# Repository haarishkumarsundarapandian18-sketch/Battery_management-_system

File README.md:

# Battery_management-_system

# CubeSat Battery Management System (BMS)

This project presents the complete development of a **Battery Management System (BMS) for a CubeSat**, starting from battery pack selection and modeling, followed by SoC estimation and BMS circuit development, and finally PCB design, manufacturing, assembly, and testing.

The project can be followed as a step-by-step workflow for developing a BMS from the initial battery requirements to a working hardware prototype.

## Project Workflow

### 1. Define Battery Requirements

Start by identifying the CubeSat's power requirements, including:

* Required battery voltage
* Required capacity
* Maximum and minimum load current
* Charging requirements
* Operating temperature range
* Expected discharge duration

These values are used to determine the required battery configuration and BMS specifications.

### 2. Design the Battery Pack

Select the appropriate battery cell based on the required voltage, capacity, discharge current, size, weight, and application requirements.

Determine the required **series (S) and parallel (P) configuration** and calculate:

* Pack voltage
* Pack capacity
* Maximum current
* Energy capacity

### 3. Build the Battery Model in MATLAB/Simulink

Create a battery model in **MATLAB/Simulink** using the selected cell characteristics.

Simulate the battery under different load conditions and observe:

* Battery voltage
* Current
* State of Charge (SoC)
* Discharge characteristics
* Battery response to changing loads

This step helps validate the battery configuration before moving to hardware development.

### 4. Implement SoC Estimation

Develop the **State of Charge estimation** model in MATLAB.

Use the battery voltage/current data and an appropriate estimation method to determine the remaining battery capacity during operation.

Test the SoC estimation model under different charge and discharge conditions and compare the estimated SoC with the expected battery behavior.

### 5. Develop the BMS Architecture

Define the BMS functions required for the battery pack.

The BMS architecture includes:

* Cell voltage monitoring
* Current sensing
* Temperature monitoring
* SoC estimation
* Battery protection
* Fault detection
* Control and communication

Define the required operating limits for each parameter.

### 6. Design the BMS Circuit

Select the required sensing, protection, control, and power-management components.

Develop the BMS schematic based on the defined architecture and connect:

* Voltage sensing circuits
* Current sensing circuit
* Temperature sensing
* Protection circuitry
* Power supply/regulation
* Controller/interface circuitry

Verify the circuit calculations and component ratings before PCB implementation.

### 7. Design the PCB in KiCad

Create the complete PCB using **KiCad**.

The process includes:

1. Creating the schematic
2. Assigning footprints
3. Creating the PCB layout
4. Placing components
5. Routing power and signal traces
6. Applying appropriate design rules
7. Checking clearances and track widths
8. Running Design Rule Checks (DRC)
9. Preparing the final PCB for manufacturing

Special attention is given to high-current paths, grounding, component placement, thermal considerations, and signal integrity.

### 8. PCB Manufacturing

Generate the required manufacturing files from KiCad and send the design for PCB fabrication.

After receiving the fabricated PCB:

* Inspect the board
* Verify footprints and connections
* Procure the required components
* Solder the components
* Inspect solder joints
* Check for shorts and incorrect connections

### 9. Hardware Testing

Power up the assembled BMS gradually and verify the individual sections before connecting the complete battery pack.

Test:

* Voltage sensing
* Current measurement
* Temperature measurement
* SoC estimation
* Protection functions
* Controller operation
* Communication/interface functions

Compare the measured hardware results with the MATLAB simulations and calculated values.

## Tools Used

* **MATLAB / Simulink** – Battery modeling and SoC estimation
* **KiCad** – Schematic capture and PCB design
* **PCB Fabrication & Assembly** – Hardware implementation
* **Battery Modeling** – Cell and pack characterization
* **BMS Design** – Monitoring and protection
* **Hardware Testing** – Validation of the developed system

## Overall Development Flow

**Battery Requirements → Battery Selection → Battery Pack Design → MATLAB Battery Modeling → SoC Estimation → BMS Architecture → Circuit Design → KiCad Schematic → PCB Layout → Manufacturing → Assembly → Testing & Validation**
# CubeSat Battery Management System (BMS)

This project presents the complete development of a **Battery Management System (BMS) for a CubeSat**, starting from battery pack selection and modeling, followed by SoC estimation and BMS circuit development, and finally PCB design, manufacturing, assembly, and testing.

The project can be followed as a step-by-step workflow for developing a BMS from the initial battery requirements to a working hardware prototype.

## Project Workflow

### 1. Define Battery Requirements

Start by identifying the CubeSat's power requirements, including:

* Required battery voltage
* Required capacity
* Maximum and minimum load current
* Charging requirements
* Operating temperature range
* Expected discharge duration

These values are used to determine the required battery configuration and BMS specifications.

### 2. Design the Battery Pack

Select the appropriate battery cell based on the required voltage, capacity, discharge current, size, weight, and application requirements.

Determine the required **series (S) and parallel (P) configuration** and calculate:

* Pack voltage
* Pack capacity
* Maximum current
* Energy capacity

### 3. Build the Battery Model in MATLAB/Simulink

Create a battery model in **MATLAB/Simulink** using the selected cell characteristics.

Simulate the battery under different load conditions and observe:

* Battery voltage
* Current
* State of Charge (SoC)
* Discharge characteristics
* Battery response to changing loads

This step helps validate the battery configuration before moving to hardware development.

### 4. Implement SoC Estimation

Develop the **State of Charge estimation** model in MATLAB.

Use the battery voltage/current data and an appropriate estimation method to determine the remaining battery capacity during operation.

Test the SoC estimation model under different charge and discharge conditions and compare the estimated SoC with the expected battery behavior.

### 5. Develop the BMS Architecture

Define the BMS functions required for the battery pack.

The BMS architecture includes:

* Cell voltage monitoring
* Current sensing
* Temperature monitoring
* SoC estimation
* Battery protection
* Fault detection
* Control and communication

Define the required operating limits for each parameter.

### 6. Design the BMS Circuit

Select the required sensing, protection, control, and power-management components.

Develop the BMS schematic based on the defined architecture and connect:

* Voltage sensing circuits
* Current sensing circuit
* Temperature sensing
* Protection circuitry
* Power supply/regulation
* Controller/interface circuitry

Verify the circuit calculations and component ratings before PCB implementation.

### 7. Design the PCB in KiCad

Create the complete PCB using **KiCad**.

The process includes:

1. Creating the schematic
2. Assigning footprints
3. Creating the PCB layout
4. Placing components
5. Routing power and signal traces
6. Applying appropriate design rules
7. Checking clearances and track widths
8. Running Design Rule Checks (DRC)
9. Preparing the final PCB for manufacturing

Special attention is given to high-current paths, grounding, component placement, thermal considerations, and signal integrity.

### 8. PCB Manufacturing

Generate the required manufacturing files from KiCad and send the design for PCB fabrication.

After receiving the fabricated PCB:

* Inspect the board
* Verify footprints and connections
* Procure the required components
* Solder the components
* Inspect solder joints
* Check for shorts and incorrect connections

### 9. Hardware Testing

Power up the assembled BMS gradually and verify the individual sections before connecting the complete battery pack.

Test:

* Voltage sensing
* Current measurement
* Temperature measurement
* SoC estimation
* Protection functions
* Controller operation
* Communication/interface functions

Compare the measured hardware results with the MATLAB simulations and calculated values.

## Tools Used

* **MATLAB / Simulink** – Battery modeling and SoC estimation
* **KiCad** – Schematic capture and PCB design
* **PCB Fabrication & Assembly** – Hardware implementation
* **Battery Modeling** – Cell and pack characterization
* **BMS Design** – Monitoring and protection
* **Hardware Testing** – Validation of the developed system

## Overall Development Flow

**Battery Requirements → Battery Selection → Battery Pack Design → MATLAB Battery Modeling → SoC Estimation → BMS Architecture → Circuit Design → KiCad Schematic → PCB Layout → Manufacturing → Assembly → Testing & Validation**

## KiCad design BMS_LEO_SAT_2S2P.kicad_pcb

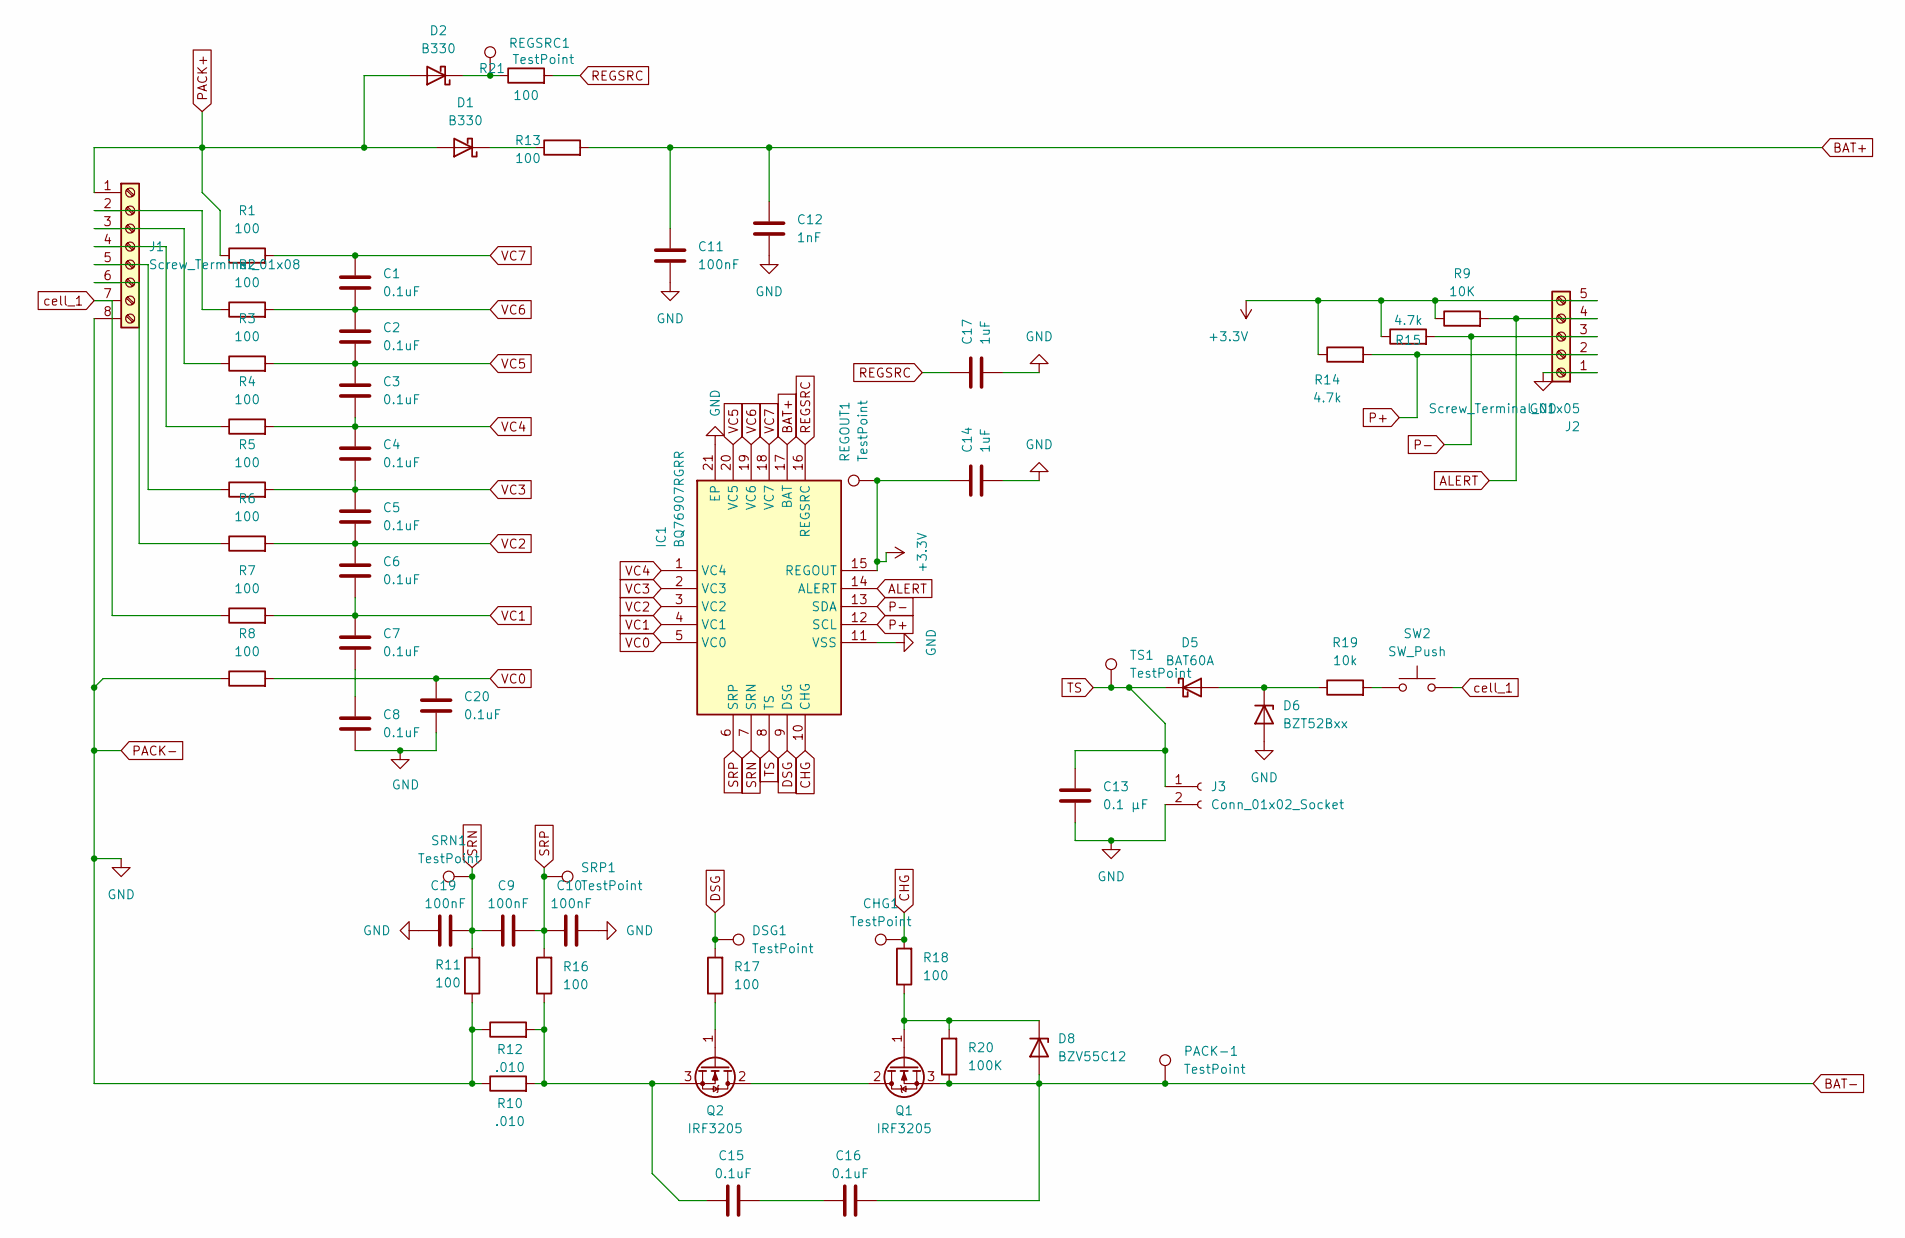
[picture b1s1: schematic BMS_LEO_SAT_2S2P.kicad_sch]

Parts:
C1, C2, C3, C4, C5, C6, C7, C8, C15, C16, C20: 0.1uF; C_0603_1608Metric_Pad1.08x0.95mm_HandSolder
C9, C10, C11, C19: 100nF; C_0603_1608Metric_Pad1.08x0.95mm_HandSolder
C12: 1nF; C_0603_1608Metric_Pad1.08x0.95mm_HandSolder
C13: 0.1 µF; C_0603_1608Metric_Pad1.08x0.95mm_HandSolder
C14, C17: 1uF; C_0603_1608Metric_Pad1.08x0.95mm_HandSolder
CHG1: TestPoint; PinHeader_1x01_P1.00mm_Vertical
D1, D2: B330; D_SMC
D5: BAT60A; D_SOD-323
D6: BZT52Bxx; D_SOD-123F
D8: BZV55C12; D_MiniMELF
DSG1: TestPoint; PinHeader_1x01_P1.00mm_Vertical
IC1: BQ76907RGRR; QFN50P350X350X100-21N-D; Manufacturer_Part_Number BQ76907RGRR; Mouser Part Number 595-BQ76907RGRR
J1: Screw_Terminal_01x08; TerminalBlock_Phoenix_MPT-0,5-8-2.54_1x08_P2.54mm_Horizontal
J2: Screw_Terminal_01x05; TerminalBlock_Phoenix_MPT-0,5-5-2.54_1x05_P2.54mm_Horizontal
J3: Conn_01x02_Socket; PinSocket_1x02_P2.00mm_Vertical
PACK-1: TestPoint; PinHeader_1x01_P1.00mm_Vertical
Q1, Q2: IRF3205; TO-220-3_Vertical
R1, R2, R3, R4, R5, R6, R7, R8, R11, R13, R16, R17, R18, R21: 100; R_0603_1608Metric_Pad0.98x0.95mm_HandSolder
R9: 10K; R_0603_1608Metric_Pad0.98x0.95mm_HandSolder
R10: .010; R_2512_6332Metric_Pad1.40x3.35mm_HandSolder
R12: .010; R_0603_1608Metric_Pad0.98x0.95mm_HandSolder
R14, R15: 4.7k; R_0603_1608Metric_Pad0.98x0.95mm_HandSolder
R19: 10k; R_0603_1608Metric_Pad0.98x0.95mm_HandSolder
R20: 100K; R_0603_1608Metric_Pad0.98x0.95mm_HandSolder
REGOUT1: TestPoint; PinHeader_1x01_P1.00mm_Vertical
REGSRC1: TestPoint; PinHeader_1x01_P1.00mm_Vertical
SRN1: TestPoint; PinHeader_1x01_P1.00mm_Vertical
SRP1: TestPoint; PinHeader_1x01_P1.00mm_Vertical
SW2: SW_Push; SW_SPST_CK_RS282G05A3
TS1: TestPoint; PinHeader_1x01_P1.00mm_Vertical

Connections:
+3.3V: C14.1, IC1.15 (REGOUT), J2.5, R9.1, R14.1, R15.1, REGOUT1.1
ALERT: IC1.14 (ALERT), J2.4, R9.2
BAT+: C11.1, C12.1, IC1.17 (BAT), R13.2
BAT-: C16.2, D8.2 (A), PACK-1.1, Q1.3 (S), R20.1
CHG: CHG1.1, IC1.10 (CHG), R18.2
DSG: DSG1.1, IC1.9 (DSG), R17.2
unnamed: C7.2, C8.1
unnamed: C15.2, C16.1
unnamed: D1.1 (K), R13.1
unnamed: D2.1 (K), R21.1, REGSRC1.1
unnamed: D5.2 (A), D6.1 (K), R19.1
unnamed: D8.1 (K), Q1.1 (G), R18.1, R20.2
unnamed: J1.2, R2.1
unnamed: J1.3, R3.1
unnamed: J1.4, R4.1
unnamed: J1.5, R5.1
unnamed: J1.6, R6.1
unnamed: Q1.2 (D), Q2.2 (D)
unnamed: Q2.1 (G), R17.1
unnamed: C15.1, Q2.3 (S), R10.2, R12.2, R16.1
unnamed: R19.2, SW2.1
P+: IC1.12 (SCL), J2.2, R14.2
P-: IC1.13 (SDA), J2.3, R15.2
PACK+: D1.2 (A), D2.2 (A), J1.1, R1.1
PACK-: C8.2, C10.2, C11.2, C12.2, C13.2, C14.2, C17.2, C19.1, C20.2, D6.2 (A), IC1.11 (VSS), IC1.21 (EP), J1.8, J2.1, J3.2, R8.1, R10.1, R11.1, R12.1
REGSRC: C17.1, IC1.16 (REGSRC), R21.2
SRN: C9.1, C19.2, IC1.7 (SRN), R11.2, SRN1.1
SRP: C9.2, C10.1, IC1.6 (SRP), R16.2, SRP1.1
TS: C13.1, D5.1 (K), IC1.8 (TS), J3.1, TS1.1
VC0: C20.1, IC1.5 (VC0), R8.2
VC1: C6.2, C7.1, IC1.4 (VC1), R7.2
VC2: C5.2, C6.1, IC1.3 (VC2), R6.2
VC3: C4.2, C5.1, IC1.2 (VC3), R5.2
VC4: C3.2, C4.1, IC1.1 (VC4), R4.2
VC5: C2.2, C3.1, IC1.20 (VC5), R3.2
VC6: C1.2, C2.1, IC1.19 (VC6), R2.2
VC7: C1.1, IC1.18 (VC7), R1.2
cell_1: J1.7, R7.1, SW2.2

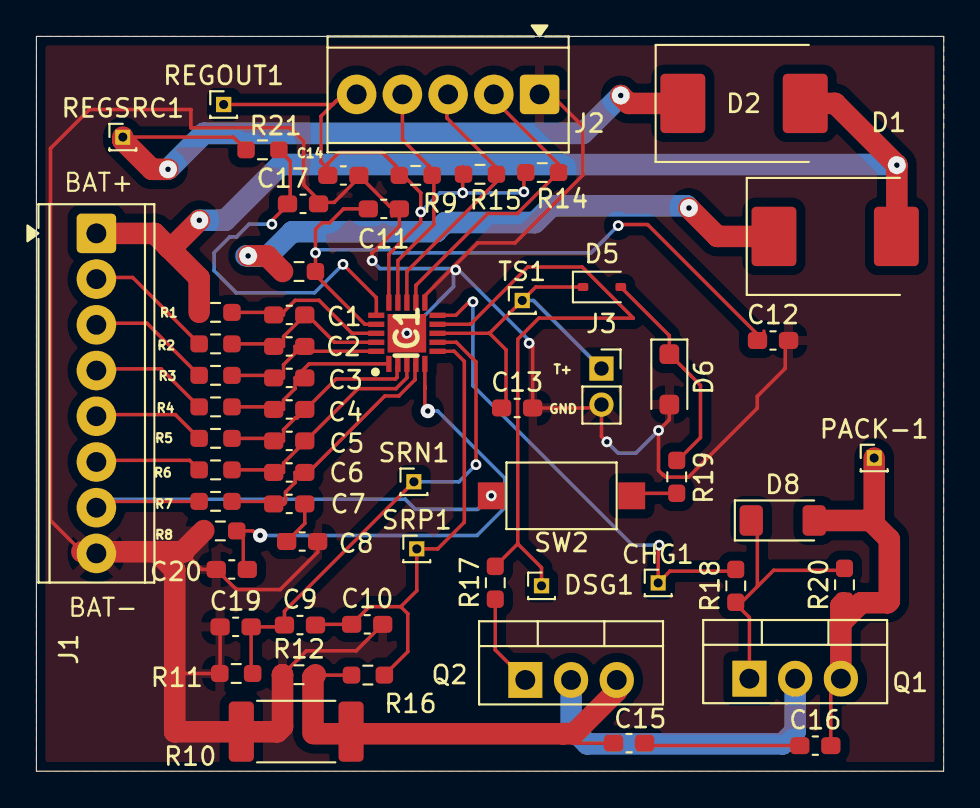
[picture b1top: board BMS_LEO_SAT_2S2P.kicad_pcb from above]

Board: 2 copper layers, 50.4 x 40.8 mm, 60 parts (0 on the bottom side), 38 nets.
